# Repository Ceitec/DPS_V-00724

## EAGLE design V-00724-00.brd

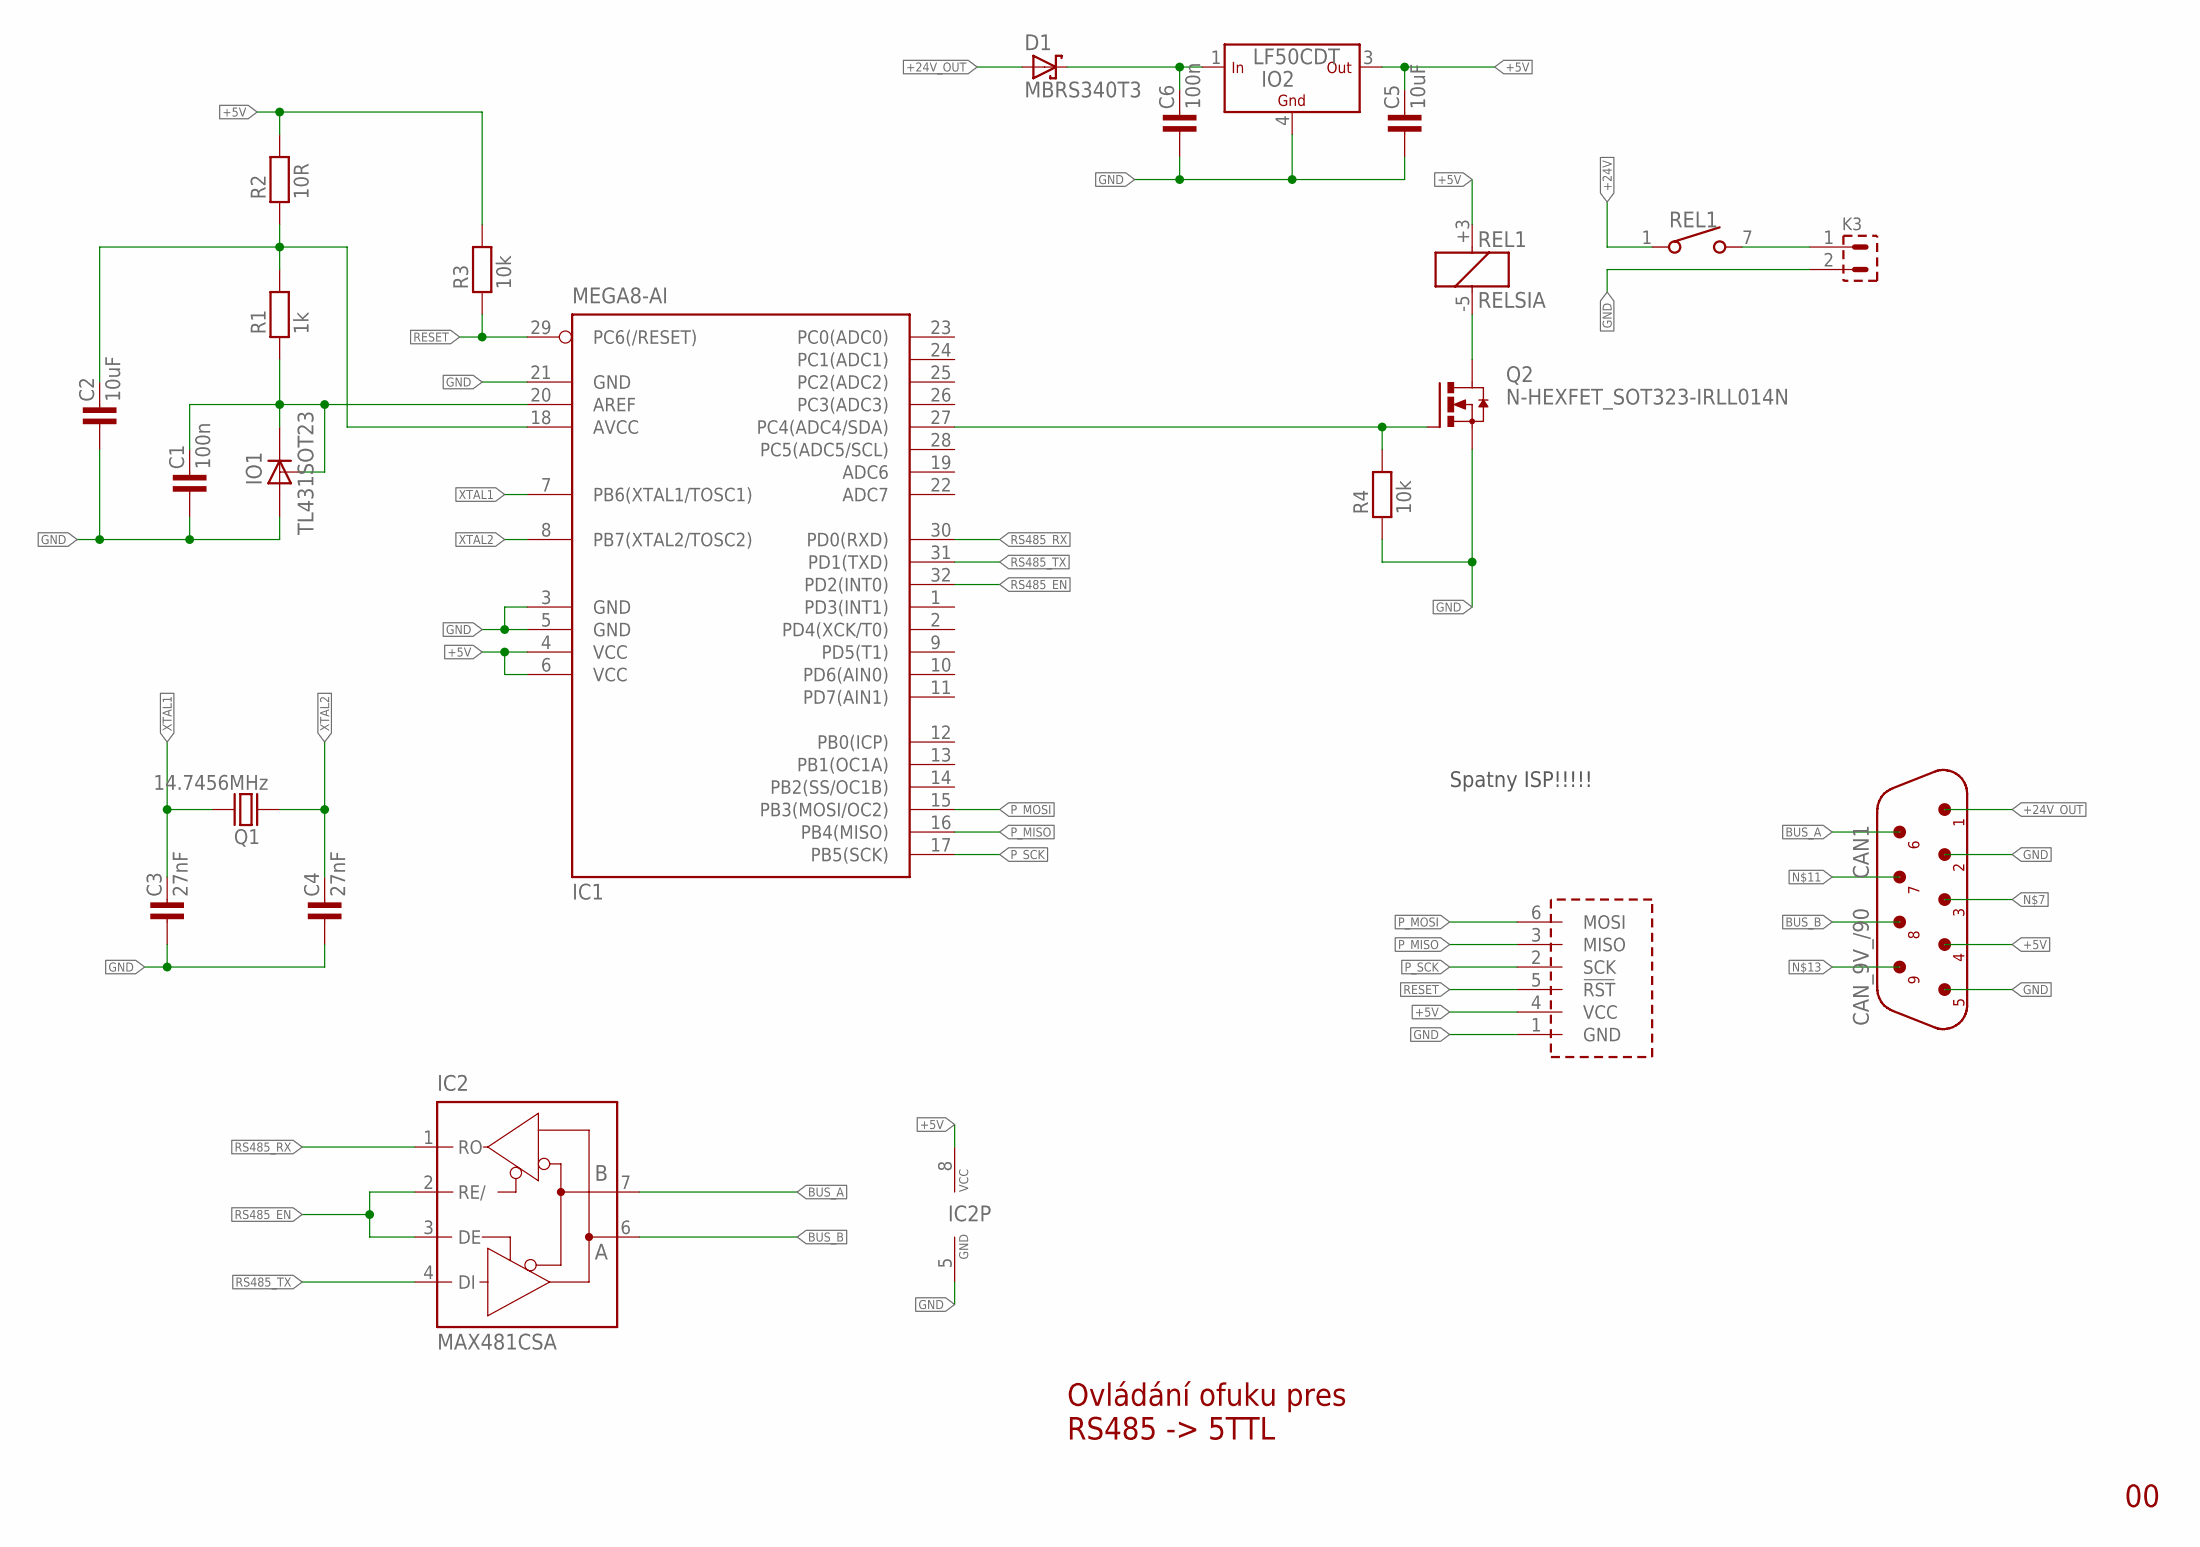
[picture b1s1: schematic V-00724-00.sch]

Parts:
C1, C6: 100n; 1206
C2, C5: 10uF; 1206
C3, C4: 27nF; 0805
CAN1: CAN_9V_/90; CAN9V/90
D1: MBRS340T3; SMC
IC1: MEGA8-AI; TQFP32-08
IC2: MAX481CSA; SO08
IO1: TL431SOT23; SOT23
IO2: LF50CDT; DPAK
K3: PSH02-02P
Q1: 14.7456MHz; HC-49U
Q2: N-HEXFET_SOT323-IRLL014N; SOT223
R1: 1k; 1206
R2: 10R; 1206
R3, R4: 10k; 1206
REL1: RELSIA
U$1: AVR_PROG_SPI; PSH02-06P

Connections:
+5V: C5.2, CAN1.4, IC1.4 (VCC), IC1.6 (VCC), IC2.8 (VCC), IO2.3 (OUT), R2.2, R3.2, REL1.+3 (C+), U$1.4 (VCC)
+24V: C6.2, D1.C, IO2.1 (IN), REL1.1
+24V_OUT: CAN1.1, D1.A
BUS_A: CAN1.6, IC2.7 (B)
BUS_B: CAN1.8, IC2.6 (A)
GND: C1.1, C2.1, C3.1, C4.1, C5.1, C6.1, CAN1.2, CAN1.5, IC1.3 (GND), IC1.5 (GND), IC1.21 (GND), IC2.5 (GND), IO1.3 (A), IO2.4 (GND), K3.2, Q2.3 (S), R4.1, U$1.1 (GND)
unnamed: C1.2, IC1.20 (AREF), IO1.1 (C), IO1.2 (R), R1.1
unnamed: C2.2, IC1.18 (AVCC), R1.2, R2.1
unnamed: IC1.27 (PC4(ADC4/SDA)), Q2.1 (G), R4.2
unnamed: Q2.4 (D), REL1.-5 (C-)
unnamed: K3.1, REL1.7 (2)
P_MISO: IC1.16 (PB4(MISO)), U$1.3 (MISO)
P_MOSI: IC1.15 (PB3(MOSI/OC2)), U$1.6 (MOSI)
P_SCK: IC1.17 (PB5(SCK)), U$1.2 (SCK)
RESET: IC1.29 (PC6(/RESET)), R3.1, U$1.5 (!RST)
RS485_EN: IC1.32 (PD2(INT0)), IC2.2 (RE/), IC2.3 (DE)
RS485_RX: IC1.30 (PD0(RXD)), IC2.1 (RO)
RS485_TX: IC1.31 (PD1(TXD)), IC2.4 (DI)
XTAL1: C3.2, IC1.7 (PB6(XTAL1/TOSC1)), Q1.2
XTAL2: C4.2, IC1.8 (PB7(XTAL2/TOSC2)), Q1.1

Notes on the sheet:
Ovládání ofuku pres RS485 -> 5TTL
Spatny ISP!!!!!

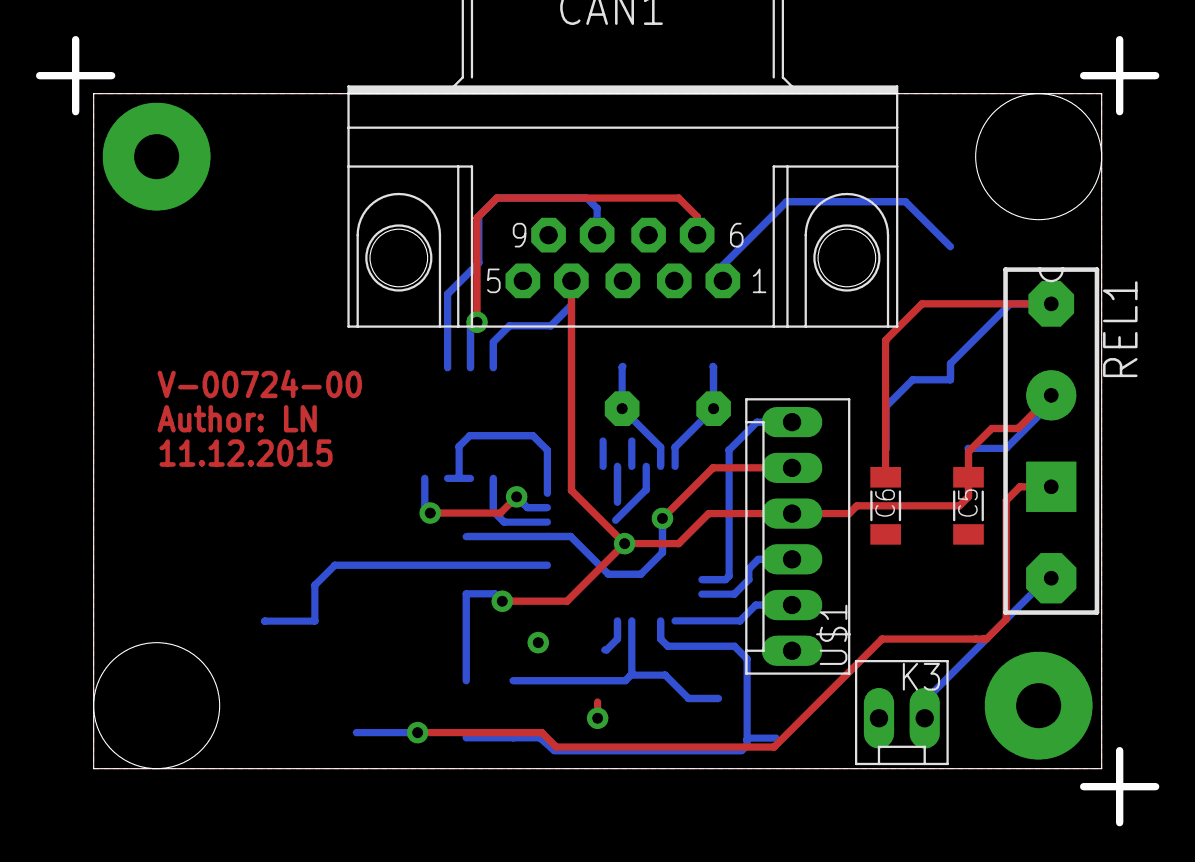
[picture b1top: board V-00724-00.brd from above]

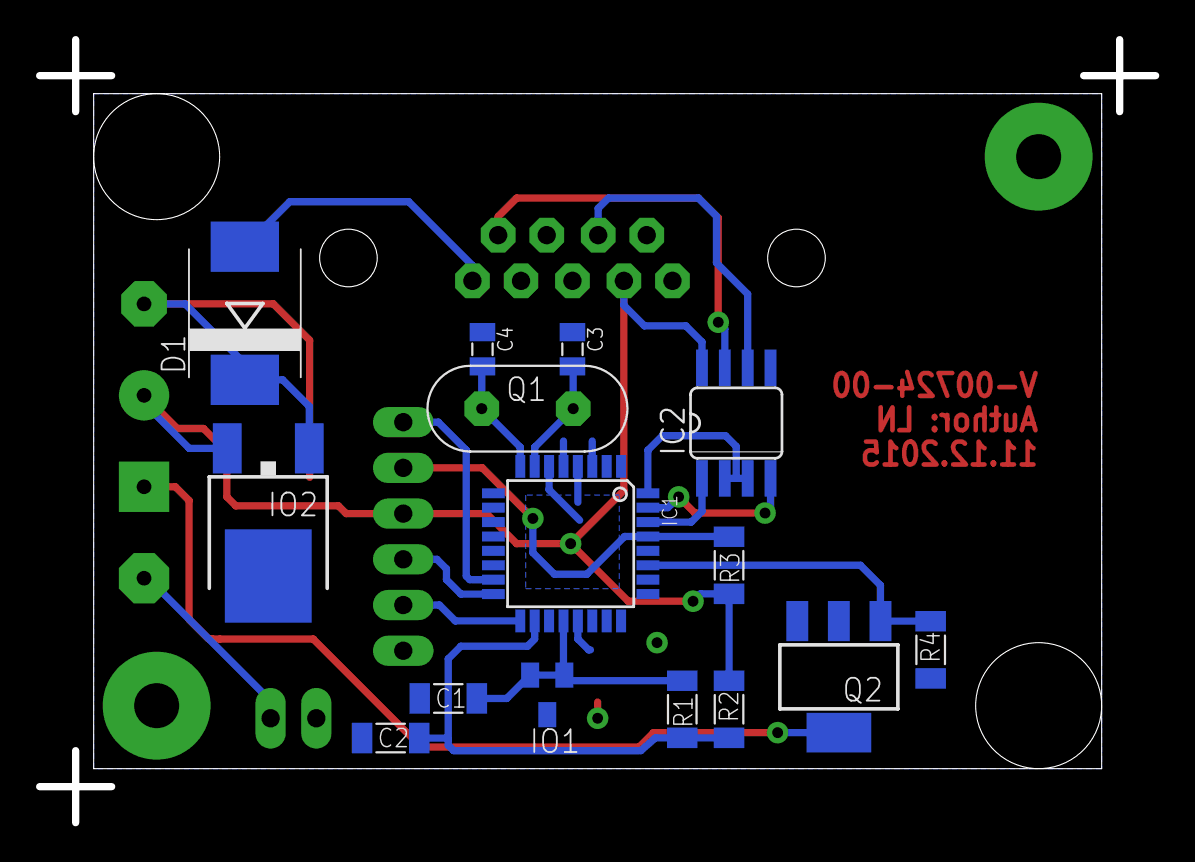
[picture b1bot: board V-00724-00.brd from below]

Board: 2 copper layers, 62.0 x 43.5 mm, 21 parts (15 on the bottom side), 20 nets.

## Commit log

2015-11-30 :octocat: Added .gitattributes & .gitignore files
2015-11-30 Ovládání ofuku přes RS485
2015-12-11 v1.1.0.1
2015-12-29 v1.1.0.2
2016-02-10 v.2.0

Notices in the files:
parts and their libraries:
Copyright (C) PaJa 2001-2014
Copyright (C) PaJa 2011-2014
